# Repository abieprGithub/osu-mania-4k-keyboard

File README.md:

# 🕹️ Hackpad | osu!mania 4K keyboard

As the name suggest, this is a hackpad that is tuned for osu!mania (the keyboard rhythm game), and only has four keys!
<br><br>

*Note: following image is still just the PCB, will update soon once the CAD is complete.*

<br<br>

For some background, this is technically not my first hackclub project.
I've circled the idea of following the Hackpad mission for some time now, and at the same time, I started playing the game [**osu!mania**](https://www.youtube.com/results?search_query=osu!mania) competitively, while using my laptop's keyboard. After one million taps on a single set of four keys, I finally decided to make one.
Additionally, while my ThinkPad's keyboard is awesome, the actuation force is actually quite heavy (60-70g), which heavily affected my endurance.
<br>

**In summary, this gives the benefit of:**
1) Preventing wear and tear on my keyboard
2) Keeping my hands from breaking apart
3) All the knowledge gained from a stardance hardware project.

<br><br><br>

## ⚙️ Features & Specifications
<br>

(Function diagram TBA)

**Dimensions: 100*42mm**
Made to maximize spacing between the left and right keys

**Peripherals: OLED Display, Rotary Encoder, 4x Standard Cherry MX switches**

**MCU: Seeeed Studio Xiao RP2040**

**Lighting: Per-key SK6812-MINI-E RGB LEDs**

**SMD footprint: 0805 Handsolder**
<br><br><br>

## 🛠️ Build your own

<br>

The assembly process follows a standard hackpad:
1) Order the PCB from JLCPCB (or another fab)
2) Solder all the parts (Although there were smd components, they're all in 0805 handsolder footprints)
3) 3D-print the case
4) Assemble the case, PCB, switches, and OLED display.
5) Upload the firmware.
<br>
All the necessary files are provided in this repository, so go take a look around before doing so.
<br>

### 📜 BOM
1) 1* Seeeed Studio XIAO RP2040
2) 1* EC11 Rotary Encoder (vertical)
3) 1* 128*32 0.91" OLED display
4) 4* Cherry MX-compatible switches
5) 4* SK6812-MINI-E Reverse mount ARGB LEDs
6) 4* 100nF 0805 Capacitors
7) 10* 10K 0805 Resistors
8) 1* 220R 0805 Resistors (optional, bridge R5 if not used)
9) 4* M3 Threaded inserts
10) 4* M3*16 screws
11) 3D printed case
12) 3D printed rotary encoder knob

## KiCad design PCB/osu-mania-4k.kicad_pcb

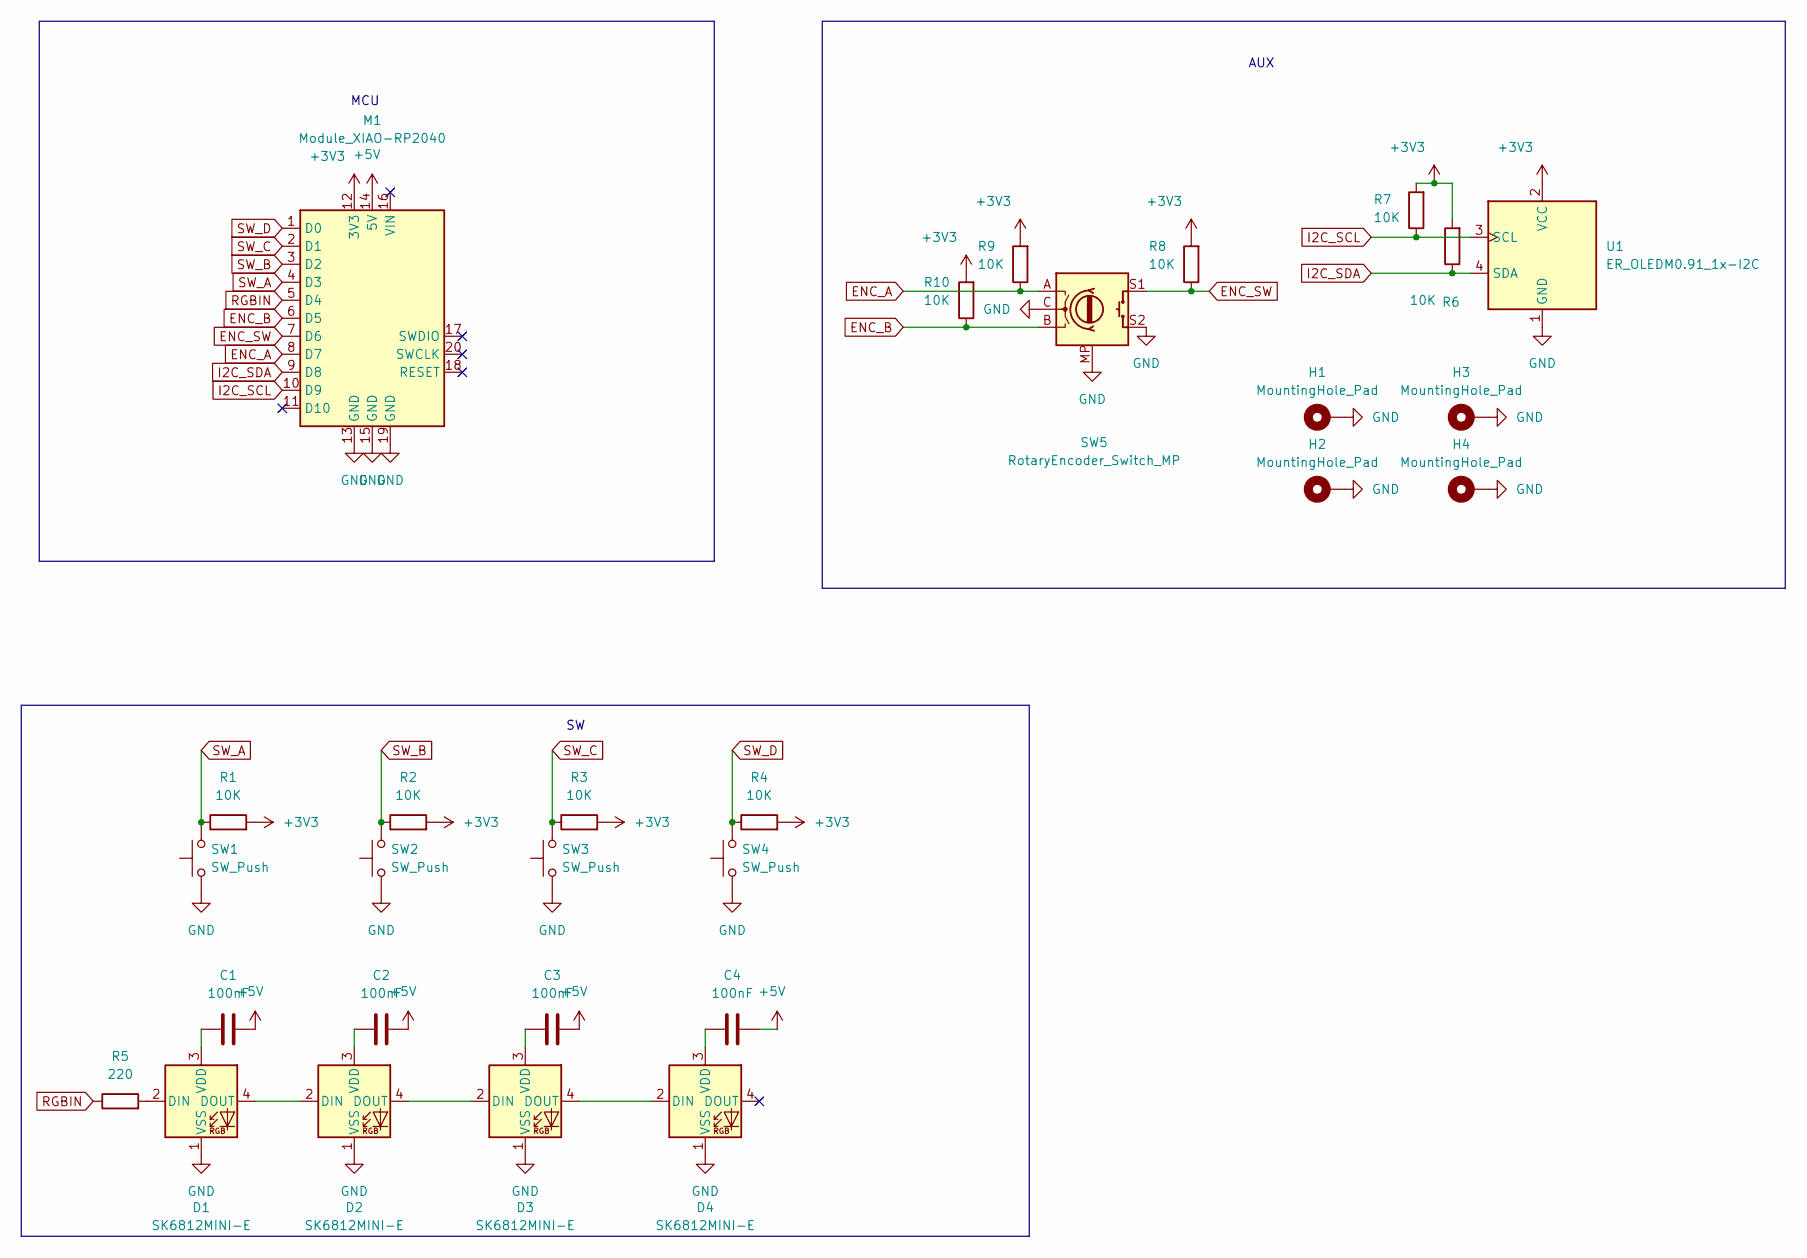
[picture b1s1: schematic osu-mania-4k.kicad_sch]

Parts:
C1, C2, C3, C4: 100nF; C_0805_2012Metric_Pad1.18x1.45mm_HandSolder
D1, D2, D3, D4: SK6812MINI-E; LED_SK6812MINI-E_3.2x2.8mm_P1.5mm_ReverseMount
H1, H2, H3, H4: MountingHole_Pad; MountingHole_3.2mm_M3_Pad_Via
M1: Module_XIAO-RP2040; SeeedStudio_XIAO_RP2040
R1, R2, R3, R4, R6, R7, R8, R9, R10: 10K; R_0805_2012Metric_Pad1.15x1.40mm_HandSolder
R5: 220; R_0805_2012Metric_Pad1.15x1.40mm_HandSolder
SW1, SW2, SW3, SW4: SW_Push; SW_Cherry_MX_PCB_1.00u
SW5: RotaryEncoder_Switch_MP; RotaryEncoder_Alps_EC11E-Switch_Vertical_H20mm_MountingHoles
U1: ER_OLEDM0.91_1x-I2C

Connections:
+3V3: M1.12 (3V3), R1.2, R2.2, R3.2, R4.2, R6.2, R7.2, R8.2, R9.2, R10.2, U1.2 (VCC)
+5V: C1.2, C2.2, C3.2, C4.2, M1.14 (5V)
ENC_A: M1.8 (D7), R9.1, SW5.A
ENC_B: M1.6 (D5), R10.1, SW5.B
ENC_SW: M1.7 (D6), R8.1, SW5.S1
GND: D1.1 (VSS), D2.1 (VSS), D3.1 (VSS), D4.1 (VSS), H1.1 (1_1), H2.1 (1_1), H3.1 (1_1), H4.1 (1_1), M1.13 (GND), M1.15 (GND), M1.19 (GND), SW1.1, SW2.1, SW3.1, SW4.1, SW5.C, SW5.MP, SW5.S2, U1.1 (GND)
I2C_SCL: M1.10 (D9), R7.1, U1.3 (SCL)
I2C_SDA: M1.9 (D8), R6.1, U1.4 (SDA)
unnamed: D1.2 (DIN), R5.2
unnamed: D1.4 (DOUT), D2.2 (DIN)
unnamed: C1.1, D1.3 (VDD)
unnamed: D2.4 (DOUT), D3.2 (DIN)
unnamed: C2.1, D2.3 (VDD)
unnamed: D3.4 (DOUT), D4.2 (DIN)
unnamed: C3.1, D3.3 (VDD)
unnamed: C4.1, D4.3 (VDD)
RGBIN: M1.5 (D4), R5.1
SW_A: M1.4 (D3), R1.1, SW1.2
SW_B: M1.3 (D2), R2.1, SW2.2
SW_C: M1.2 (D1), R3.1, SW3.2
SW_D: M1.1 (D0), R4.1, SW4.2

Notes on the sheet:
AUX
MCU

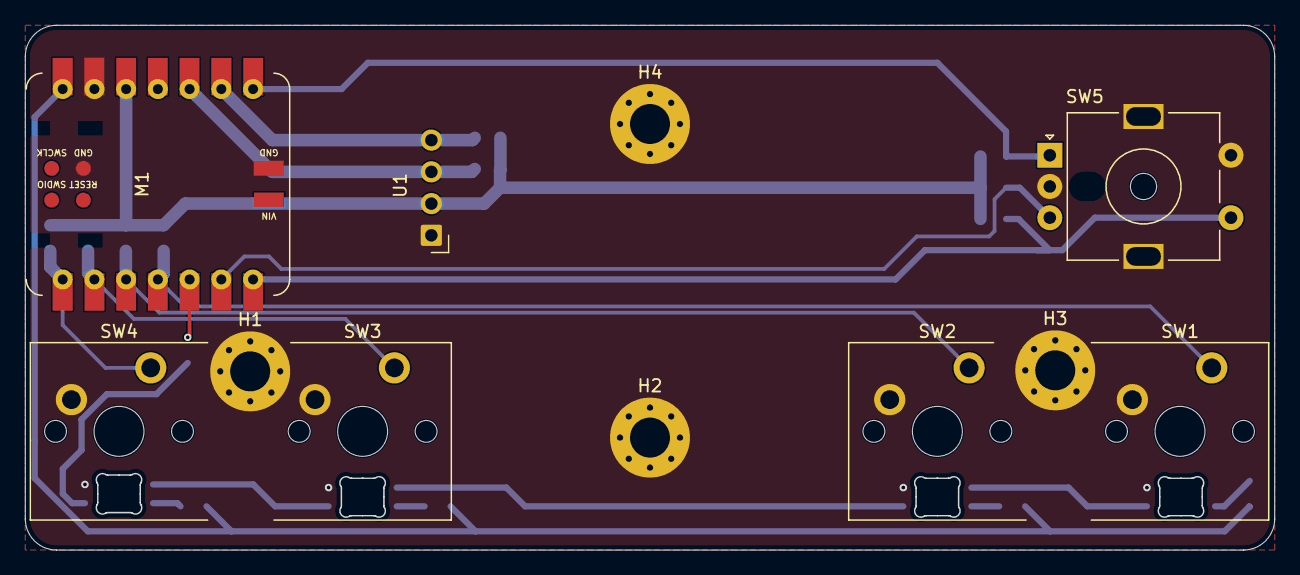
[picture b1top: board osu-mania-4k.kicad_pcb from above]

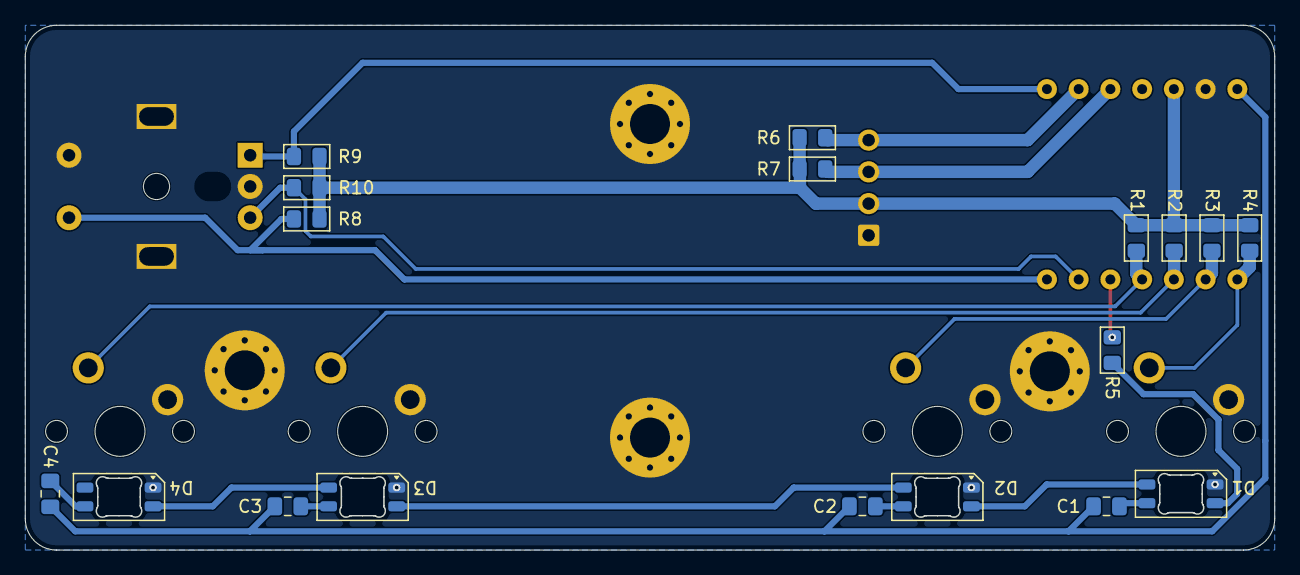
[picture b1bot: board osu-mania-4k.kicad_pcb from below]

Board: 2 copper layers, 100.0 x 42.0 mm, 29 parts (18 on the bottom side), 21 nets.
